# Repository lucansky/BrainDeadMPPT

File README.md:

# Simple MPPT Battery charger

Because f-ck complex things.

Is 4-layer PCB containing [LTC4015](http://www.analog.com/media/en/technical-documentation/data-sheets/4015fb.pdf) step-down battery charger with PowerPATH. 

[**Schematic**](https://github.com/lucansky/BrainDeadMPPT/blob/master/BrainDeadMPPT.pdf)

## Features:
* Automatically detects MPPT voltage of panel and other cool stuff.
* 8A current
* DIN rail mountable on [this](https://www.aliexpress.com/item/info/32800952114.html) along with [this heat transporter](https://www.aliexpress.com/item/200-400mm-0-5-1-0-2-0-3-0-4-0-5-0mm-High-Thermal/32883424736.html) in-between
* Won't break (AEC-Q100/101/200)
* Accepts max 35V solar panel
* Looks cool

## Status
* 15.8.2018: Ready for PCB production (prototype)
* 16.8.2018: In production 2x [gatema.cz](https://www.gatema.cz/plosne-spoje)

## Render

## Contact
Adam Lučanský <adamlucansky@gmail.com>

irc: #base48 with nick Adluc @ freenode.net

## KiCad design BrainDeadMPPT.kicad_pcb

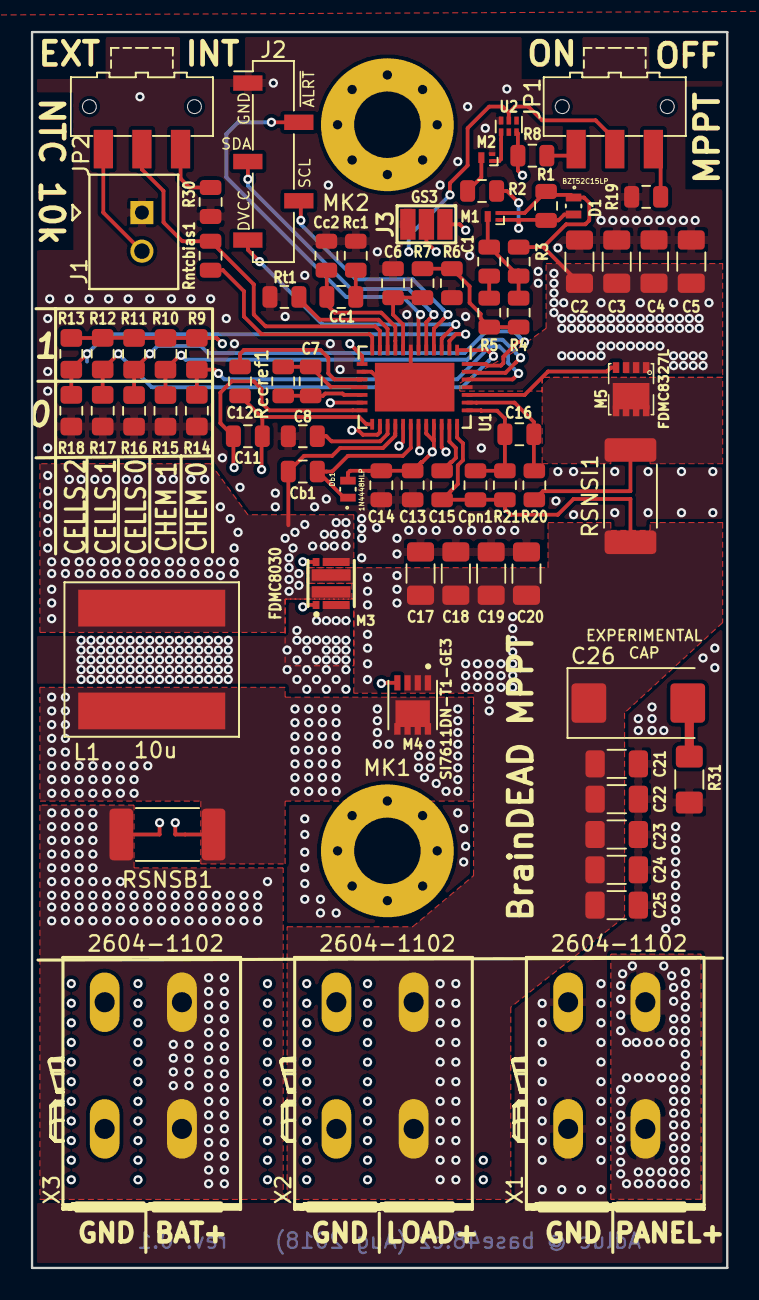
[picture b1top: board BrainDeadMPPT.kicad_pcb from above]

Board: 4 copper layers, 45.0 x 80.0 mm, 77 parts (0 on the bottom side), 48 nets.

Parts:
C1: 2200p; C_0805_2012Metric
C2, C3, C4, C5, C18, C19, C20, C21, C22, C23, C24, C25: 10u; C_1206_3216Metric
C6: 100p; C_0805_2012Metric
C7, C13, C14: 0.1u; C_0805_2012Metric
C8: 2.2u; C_0805_2012Metric
C11, C16: 1000p; C_0805_2012Metric
C12, C15: 0.33u; C_0805_2012Metric
C17: 0.1u; C_1206_3216Metric
C26: 120u; CP_EIA-7343-43_Kemet-X_Pad2.25x2.55mm_HandSolder
Cb1: 0.47u; C_0805_2012Metric
Cc1: 0.22u; C_0805_2012Metric
Cc2: 0.01u; C_0805_2012Metric
Cpn1: 1u; C_0805_2012Metric
D1: BZT52C15LP; DFN160X100X57-2N
Db1: 1N4448HLP; DFN160X100X57-2N
J1: Conn_01x02; JST_B2B-XH-A
J2: Conn_01x05; PinSocket_1x05_P2.54mm_Vertical_SMD_Pin1Left
J3: GS3; SMD-solder-bridge-3pin
JP1, JP2: Jumper_NC_Dual; SW_SPDT_CK-JS102011SAQN
L1: 10u; INDC110100X1000N
M1: DMP58D0LFB; Diodes_DFN1006-3
M2: DMN62D1SFB; Diodes_DFN1006-3
M3: FDMC8030; TRANS_FDMC8030
M4: SI7611DN-T1-GE3; VISHAY_SIS468DN-T1-GE3
M5: FDMC8327L; MLP8L33
MK1, MK2: Mounting_Hole_PAD; MountingHole_4.3mm_M4_Pad_Via
R1: 47k; R_0805_2012Metric
R2, R7, R30: 10k; R_0805_2012Metric
R3: 226k; R_0805_2012Metric
R4: 64.9k; R_0805_2012Metric
R5, R20, R21: 0; R_0805_2012Metric
R6: 10.0k; R_0805_2012Metric
R8: 1k; R_0805_2012Metric
R9, R10, R11, R12, R13, R14, R15, R16, R17, R18: 0; R_0805_2012Metric_Pad1.15x1.40mm_HandSolder
R19: 1M; R_0805_2012Metric
R31: 0.05; R_1206_3216Metric_Pad1.42x1.75mm_HandSolder
RSNSB1: R; R_2512_6332Metric_Pad1.52x3.35mm_HandSolder
RSNSI1: 0.003; R_2512_6332Metric_Pad1.52x3.35mm_HandSolder
Rc1: 200; R_0805_2012Metric
Rccref1: 301k; R_0805_2012Metric
Rntcbias1: 10.0k; R_0805_2012Metric
Rt1: 95.3k; R_0805_2012Metric
U1: LTC4015EUHF; QFN-38-1EP_5x7mm_P0.5mm_EP3.15x5.15mm
U2: NC7SZ04L6X; Fairchild_MicroPak-6_1.0x1.45mm_P0.5mm
X1, X2, X3: 2604-1102; con-wago_2604-P-2604-1102_cutoff

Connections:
/BAT_PRESENSE: C11.1, C12.2, L1.2, M4.5, M4.6, M4.7, M4.8, M4.9, RSNSB1.1, U1.20
/CELLS0: R11.2, R16.1, U1.38
/CELLS1: R12.2, R17.1, U1.1
/CELLS2: R13.2, R18.1, U1.2
/CHEM0: R9.2, R14.1, U1.36
/CHEM1: R10.2, R15.1, U1.37
/DVCC: J2.5, U1.3
/ISNS: M5.5, M5.6, M5.7, M5.8, M5.F1, R20.2, RSNSI1.2
/SCL: J2.4, U1.4
/SDA: J2.3, U1.5
/SW: Cb1.1, L1.1, M3.5, M3.10, U1.23
/~SMBALERT: J2.2, U1.6
BAT+: C11.2, RSNSB1.2, U1.18, U1.19, X3.P1.1, X3.P1.2
GND: C2.2, C3.2, C4.2, C5.2, C6.2, C8.2, C13.2, C14.2, C17.2, C18.2, C19.2, C20.2, C21.2, C22.2, C23.2, C24.2, C25.2, Cc2.2, J1.1, J2.1, J3.3, M2.2, M3.4, R6.2, R14.2, R15.2, R16.2, R17.2, R18.2, R19.2, R30.1, R31.1, Rc1.2, Rt1.2, U1.7, U1.14, U1.39, U2.3, X1.P2.1, X1.P2.2, X2.P2.1, X2.P2.2, X3.P2.1, X3.P2.2
INT_VCC: C13.1, C14.1, Db1.2, J3.1, R8.1, R9.1, R10.1, R11.1, R12.1, R13.1, U1.27, U1.28, U2.6
LOAD+: C15.1, C17.1, C18.1, C19.1, C20.1, C21.1, C22.1, C23.1, C24.1, C25.1, C26.1, Cpn1.1, M3.9, M4.1, M4.2, M4.3, R21.2, RSNSI1.1, U1.31, X2.P1.1, X2.P1.2
NTC: J1.2, JP2.3
unnamed: C1.1, M1.3, R3.2, R4.1
unnamed: C1.2, R5.1
unnamed: C6.1, R7.1, U1.8
unnamed: C7.1, Rccref1.1, U1.17
unnamed: C7.2, Rccref1.2, U1.16
unnamed: C8.1, U1.22
unnamed: C12.1, U1.15
unnamed: C15.2, U1.30
unnamed: C16.1, R20.1, U1.33
unnamed: C16.2, Cpn1.2, R21.1, U1.32
unnamed: C26.2, R31.2
unnamed: Cb1.2, Db1.1, U1.25
unnamed: Cc1.1, Cc2.1, U1.9
unnamed: Cc1.2, Rc1.1
unnamed: D1.2, M1.1, R1.2, R2.1
unnamed: J3.2, U1.13
unnamed: JP1.1, R19.1
unnamed: JP1.2, U1.21, U2.2
unnamed: JP1.3, R8.2
unnamed: JP2.1, R30.2
unnamed: JP2.2, Rntcbias1.2, U1.11
unnamed: M2.1, U2.4
unnamed: M2.3, R2.2
unnamed: M3.1, U1.26
unnamed: M3.8, U1.24
unnamed: M4.4, U1.29
unnamed: M5.4, U1.34
unnamed: R4.2, R5.2, R6.1, R7.2
unnamed: Rntcbias1.1, U1.12
unnamed: Rt1.1, U1.10
VIN+: C2.1, C3.1, C4.1, C5.1, D1.1, M1.2, M5.1, M5.2, M5.3, R1.1, R3.1, U1.35, X1.P1.1, X1.P1.2

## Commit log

2018-08-15 Docs: fixed amperage
2018-08-16 Readme: contact
2018-08-16 Gerbers & gatema pre-processor (renamer to be precise)
